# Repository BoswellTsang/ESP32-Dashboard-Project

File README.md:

# ESP32 E-Ink Smart Dashboard

**Status:** Completed (August 2026) · **Type:** Personal Project  
**Tools:** KiCad, ESP32, C/C++, SPI, I²C, Wi-Fi, HTTP/JSON, Arduino

> A battery-powered, 4.2-inch e-ink dashboard built from a breadboard prototype into a custom two-layer PCB. It automatically displays weather, date/time, and upcoming events from online services.

## At a glance

| Subsystem | Implementation |
| --- | --- |
| Microcontroller | ESP32 |
| Display | 4.2-inch Waveshare e-ink, SSD1683-compatible driver |
| Timekeeping | DS3231 real-time clock (I²C) |
| PCB | Custom two-layer KiCad design, fabricated and hand assembled |
| Power | LiPo battery, charging circuit and regulated 3.3 V |
| Display communication | SPI |
| Online services | Wi-Fi, HTTP/JSON, OpenWeatherMap and Notion |
| Low-power operation | Periodic ESP32 deep sleep; retained variables in RTC memory |

## Project overview

I designed and assembled a standalone dashboard to combine electronic hardware design, power management, and firmware in one working device. I initially developed the system on a breadboard, then created a custom PCB incorporating the ESP32, RTC, battery charging and regulation, reset circuitry, status LED and supporting passives. Firmware retrieves online data, updates the display and enters deep sleep between refreshes.

## Hardware development

- Captured the complete schematic and routed a custom **two-layer PCB** using KiCad.
- Designed 3.3 V distribution, LiPo charging connections, reset/status circuits, decoupling, and SPI/I²C interfaces.
- Planned component placement, trace routing and a ground copper pour.
- Fabricated, soldered, assembled and integrated the PCB with the display and firmware.

KiCad Files are published in [hardware/README.md](hardware/README.md).

## Firmware

- Communicates with the display through SPI and with the DS3231 through I²C.
- Retrieves weather and calendar data using Wi-Fi and HTTP/JSON, with OpenWeatherMap and Notion integrations.
- Formats information for the e-ink display.
- Coordinates deep-sleep wake/refresh cycles.
- Preserves required data in RTC-retained memory; fixed-size character arrays were used where dynamic string storage caused persistence problems.

**Source:** [ESP32_Dashboard_Project_Code.ino](ESP32_Dashboard_Project_Code.ino) — the existing sketch is preserved at the repository root. 

## Testing and results

| Feature | Status |
| --- | --- |
| Fabricated PCB and completed assembly | Completed |
| Weather, date/time and calendar display | Completed |
| SPI, I²C and Wi-Fi data access | Completed |
| Deep-sleep state retention | Implemented and debugged |
| Measured sleep/active current | Not documented |
| Battery runtime | Not documented |

See [test record](docs/testing.md).

## Repository guide

- [System architecture](docs/architecture.md)
- [Engineering decisions and debugging](docs/design-decisions.md)
- [Test record](docs/testing.md)
- [Project progress log](docs/progress-log.md)
- [Hardware file guide](hardware/README.md)
- [Firmware notes](firmware/README.md)

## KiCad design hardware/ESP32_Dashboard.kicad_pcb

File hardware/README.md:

# Hardware source files

The dashboard was built using a custom two-layer PCB.

# Components
| Subsystem | Implementation |
| --- | --- |
| Microcontroller | ESP32 |
| Display | 4.2-inch Waveshare e-ink, SSD1683-compatible driver |
| Timekeeping | DS3231 real-time clock (I²C) |
| Power | LiPo battery, charging circuit and regulated 3.3 V |
| API | OpenWeatherMap and Notion |

# Schematic

# PCB

# PCB 3D-View

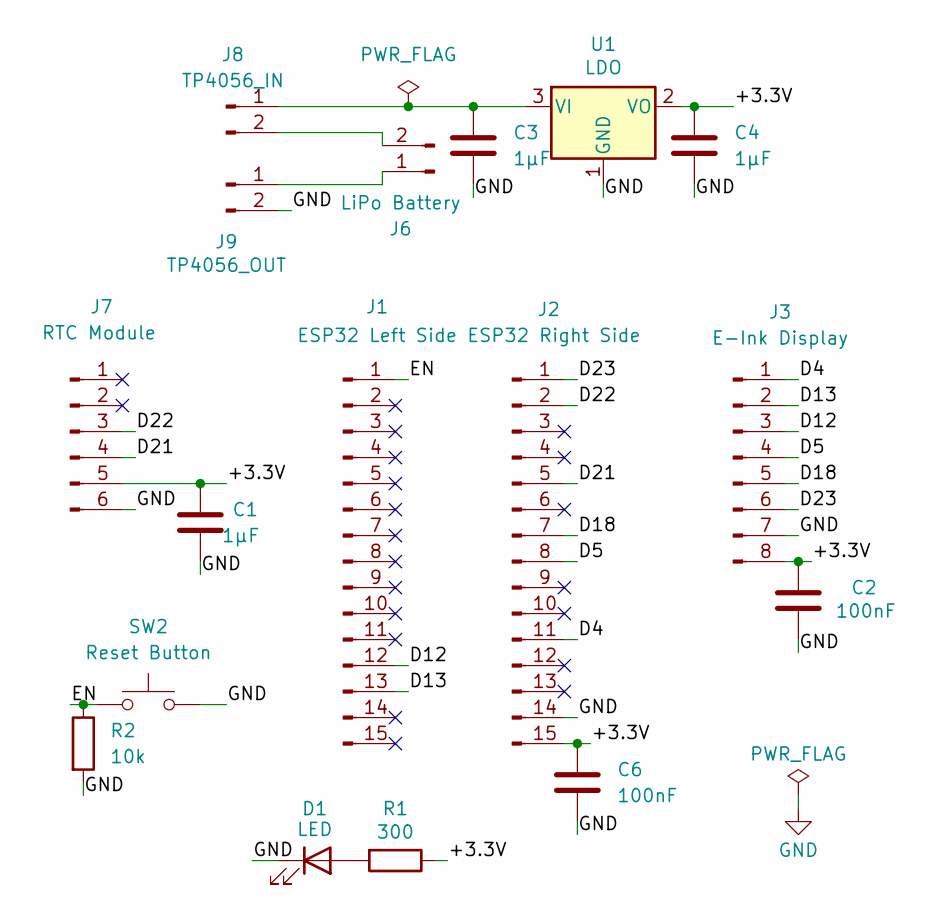
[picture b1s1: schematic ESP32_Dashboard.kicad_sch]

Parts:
C1, C3, C4: 1µF; C_Disc_D5.0mm_W2.5mm_P5.00mm
C2, C6: 100nF; C_Disc_D5.0mm_W2.5mm_P5.00mm
D1: LED; LED_D3.0mm
J1: ESP32 Left Side; PinSocket_1x15_P2.54mm_Vertical
J2: ESP32 Right Side; PinSocket_1x15_P2.54mm_Vertical
J3: E-Ink Display; PinHeader_1x08_P2.54mm_Vertical
J6: LiPo Battery; JST_PH_S2B-PH-K_1x02_P2.00mm_Horizontal
J7: RTC Module; PinSocket_1x06_P2.54mm_Vertical
J8: TP4056_IN; PinHeader_1x02_P2.54mm_Vertical
J9: TP4056_OUT; PinHeader_1x02_P2.54mm_Vertical
R1: 300; R_Axial_DIN0207_L6.3mm_D2.5mm_P7.62mm_Horizontal
R2: 10k; R_Axial_DIN0207_L6.3mm_D2.5mm_P7.62mm_Horizontal
SW2: Reset Button; SW_PUSH_6mm
U1: LDO; TO-92_Inline

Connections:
/+3.3V: C1.1, C2.1, C4.1, C6.1, J2.15, J3.8, J7.5, R1.1, U1.2 (VO)
/D4: J2.11, J3.1
/D5: J2.8, J3.4
/D12: J1.12, J3.3
/D13: J1.13, J3.2
/D18: J2.7, J3.5
/D21: J2.5, J7.4
/D22: J2.2, J7.3
/D23: J2.1, J3.6
/EN: J1.1, R2.1, SW2.1
GND: C1.2, C2.2, C3.2, C4.2, C6.2, D1.1 (K), J2.14, J3.7, J7.6, J9.2, R2.2, SW2.2, U1.1 (GND)
unnamed: D1.2 (A), R1.2
unnamed: J6.1, J9.1
unnamed: J6.2, J8.2
unnamed: C3.1, J8.1, U1.3 (VI)

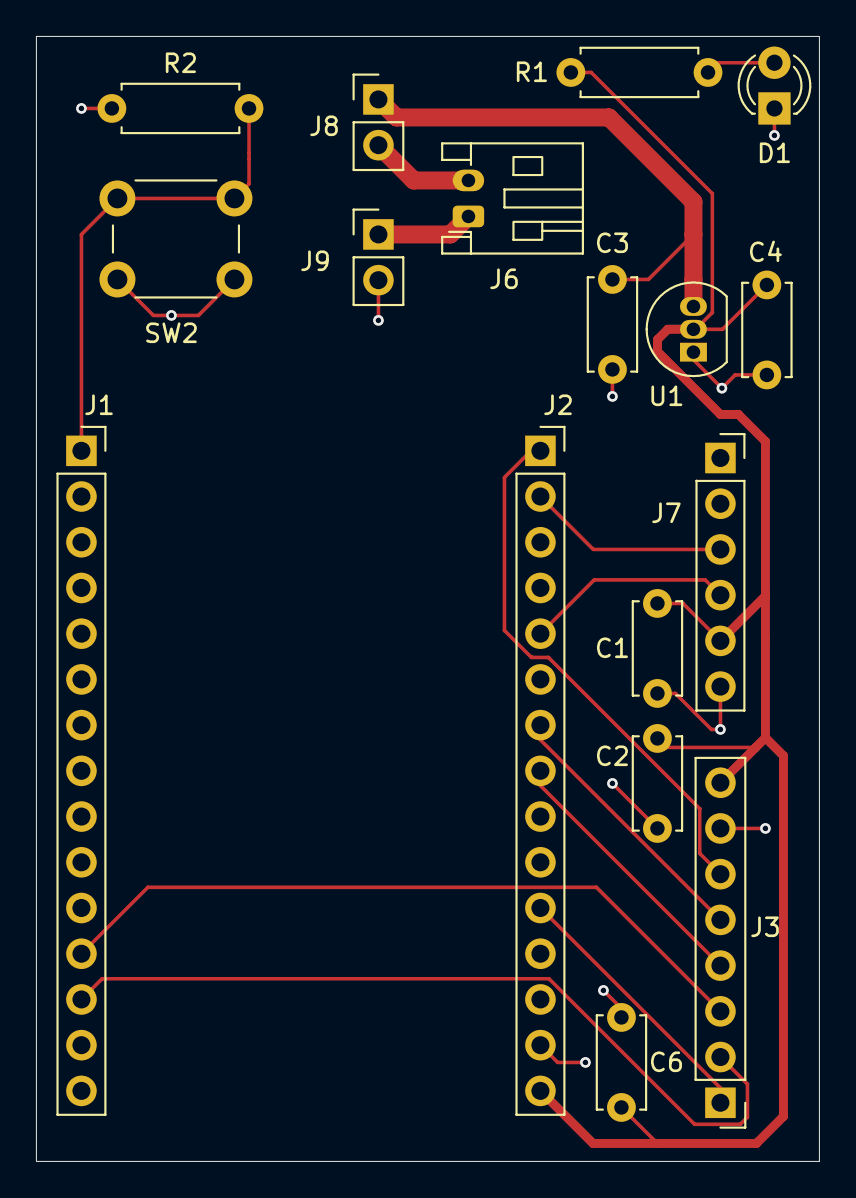
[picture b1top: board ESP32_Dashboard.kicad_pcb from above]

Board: 2 copper layers, 43.5 x 62.5 mm, 17 parts (0 on the bottom side), 15 nets.
